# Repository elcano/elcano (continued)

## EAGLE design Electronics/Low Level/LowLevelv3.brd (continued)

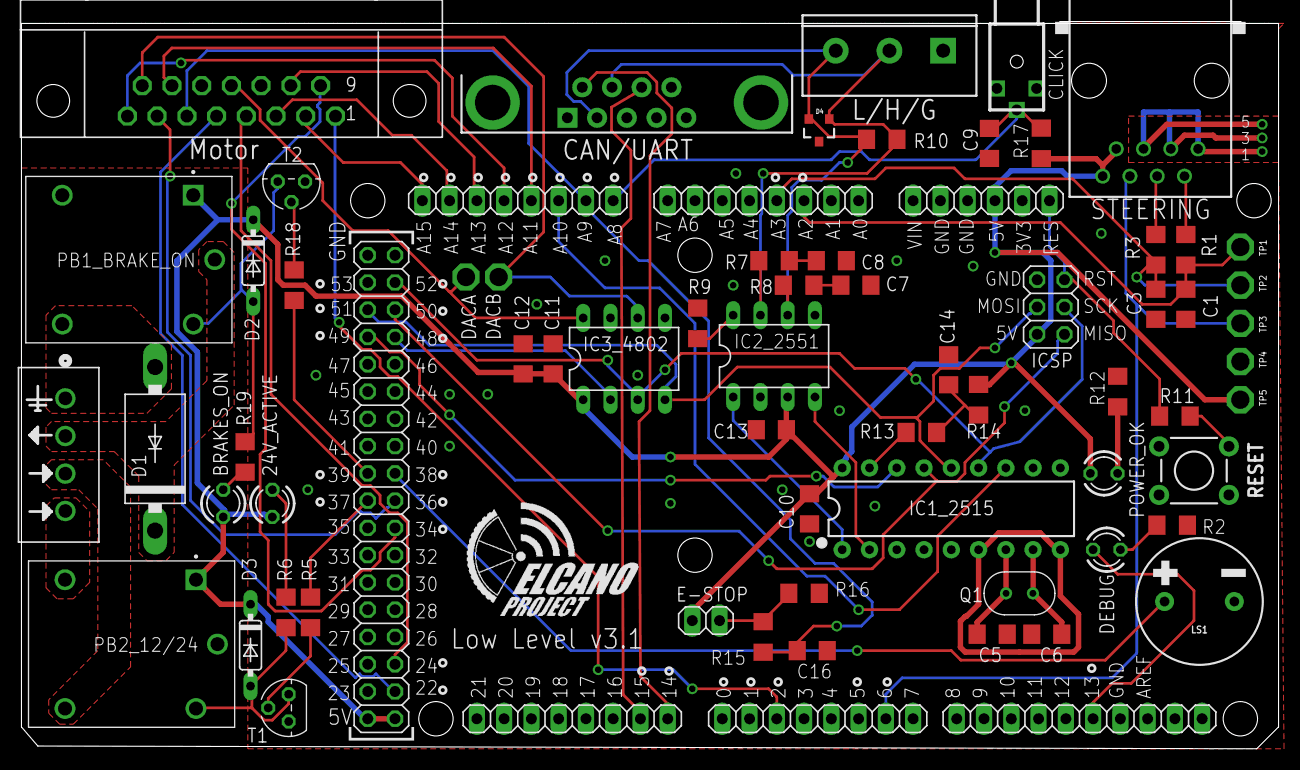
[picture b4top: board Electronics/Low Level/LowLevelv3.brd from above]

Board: 2 copper layers, 117.1 x 67.7 mm, 71 parts (0 on the bottom side), 60 nets.

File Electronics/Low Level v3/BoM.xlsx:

Qty | Device Name | Value | In BoM? | Digikey Part Number | Package | Part Label | Description | DESCRIPTION | DIGI-KEY_PART_NUMBER | DIGI-KEY_PURCHASE_URL | MANUFACTURER_PART_NUMBER | MF | MP | MPN | OC_FARNELL | OC_NEWARK | PACKAGE | PROD_ID | SF_SKU | SPICEPREFIX | VALUE | VENDOR
2 | 3mm green LED |  | yes | 732-5008-ND | LED3MM | 24V_ACTIVE, BRAKES_ON | LED
2 | C-USC1206 | 33pF | yes | 732-7873-1-ND | C1206 | C5, C6 | CAPACITOR, American symbol
2 | C-USC1206 | 560pF | yes | 311-4436-1-ND | C1206 | C7, C8 | CAPACITOR, American symbol
5 | C-USC1206 | 0.1uF | yes | 732-8086-1-ND | C1206 | C10, C11, C12, C13, C14 | CAPACITOR, American symbol
7 | C-USC1206 | 1uF | yes | 732-7685-1-ND | C1206 | C1, C2, C3, C4, C9, C15, C16 | CAPACITOR, American symbol
2 | R-US_R1206 | 100 | yes | 311-100FRCT-ND | R1206 | R7, R8 | RESISTOR, American symbol
6 | R-US_R1206 | 4.7K | yes | A106078CT-ND | R1206 | R1, R2, R3, R4, R9, R17 | RESISTOR, American symbol
4 | R-US_R1206 | 10k | yes | RMCF1206JT10K0CT-ND | R1206 | R11, R12, R15, R16 | RESISTOR, American symbol
1 | R-US_R1206 | 120 | yes | A129547CT-ND | R1206 | R10 | RESISTOR, American symbol
5 | R-US_R1206 | 1K | yes | RNCP1206FTD1K00CT-ND | R1206 | R5, R6, R13, R18, R19 | RESISTOR, American symbol
1 | R-US_R1206 | 20K | yes | RNCP1206FTD20K0CT-ND | R1206 | R14 | RESISTOR, American symbol
1 | 16MHz crystal | 16MHz | Yes | XC1759-ND | XTAL_ECS-160-20-46X | Q1 | QUARTZ CRYSTAL T/H | Crystal 16MHz ¬±30ppm _Tol_ ¬±50ppm _Stability_ 20pF FUND 50Ohm | XC1759-ND | https://www.digikey.com/product-detail/en/ecs-inc/ECS-160-20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 |  | ECS Inc. | ECS-160-20-46X |  |  |  | HC46/X ECS International |  |  | B
2 | 1N4148DO35-7 | 1N4148DO35-7 | yes | 1N4148FSCT-ND | DO35-7 | D2, D3 | DIODE
1 | 1N5400 | 1N5400 | yes | 1N5400-BDI-ND | DO201-15 | D1 | DIODE
1 | 284512-4 | 284512-4 | yes | A98398-ND | 284512-4 | X1 |  |  |  |  | 2845124 |  |  |  |  |  |  |  |  |  |  | TE Connectivity
2 | 2N3904 | 2N3904 | yes | 2N3904-APCT-ND | TO92 | T1, T2 | NPN TRANSISTOR
1 | BUZZER-PTH | BUZZER-PTH | Yes | 102-1153-ND | BUZZER-12MM | LS1 | Buzzer |  |  |  |  |  |  |  |  |  |  | COMP-08253 | COM-07950
2 | ORWH-SH-105D1F,000 | ORWH-SH-105D1F,000 | Yes | PB2032-ND | TE_ORWH-SH-105D1F,000 | PB1_BRAKE_ON, PB2_12/24 | General Purpose Relay, ORWH Series, Power, Non Latching, SPDT, 5 VDC, 10 A | General Purpose Relay, ORWH Series, Power, Non Latching, SPDT, 5 VDC, 10 A | PB2032-ND | https://www.digikey.com/product-detail/en/te-connectivity-po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 |  | TE | ORWH-SH-105D1F,000 |  |  |  | None
1 | ODO_JACK | CLICK |  |  | ODO_JACK | X4
1 | PESD1CAN | PESD1CAN | Yes | 1727-3817-1-ND | SPARKFUN-DISCRETESEMI_SOT23-3 | D4 | CAN bus ESD protection diode |  |  |  |  |  |  |  |  |  |  |  |  | J
1 | MCP2515(MCP2510)P | MCP2515 | yes | MCP2515-I/P-ND | DIP18 | IC1_2515 | CAN controller with SPI interface |  |  |  |  |  |  |  |  |  |  | NA-XXXXX |  | X | MCP2515
1 | MCP2551DIL08 | MCP2551DIL08 | Yes | MCP2551-E/P-ND‎ | IC-PACKAGE_DIL08 | IC2_2551 | CAN transceiver |  |  |  |  |  |  |  |  |  |  |  |  | X
1 | DIL8 | MCP4802 | Yes | MCP4802-E/P-ND | DIL08 | IC3_4802 | Dual In Line / Socket
1 | MOMENTARY-SWITCH-SPST-PTH-6.0MM | MOMENTARY-SWITCH-SPST-PTH-6.0MM | Yes | 450-1650-ND‎ | TACTILE_SWITCH_PTH_6.0MM | RESET | Momentary Switch (Pushbutton) - SPST |  |  |  |  |  |  |  |  |  |  | SWCH-08441 | COM-00097
1 | CONN_03-SCREW-5MM |  |  |  | SCREWTERMINAL-5MM-3 | CAN_HEADER | Multi connection point. Often used as Generic Header-pin footprint for 0.1 inch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 |  |  |  |  |  |  |  |  |  |  | CONN-10134 | PRT-08433
1 | 5-104069-4 | 5-104069-4 | yes | A107254-ND | CONN_5-104069-4_TYCO | STEERING_IO |  |  |  |  | 51040694 |  |  |  |  |  |  |  |  |  |  | TE Connectivity
1 | DB9FEMALE | DB9 Plug | Yes | 182-09ME-ND‎ | DB9 | CANBUS | DB9 Connector |  |  |  |  |  |  |  |  |  |  | CONN-08194 |  | X
1 | M15-182 | DB-15 | Yes | AE10976-ND | 182-015-MALE | X3 | SUB-D |  |  |  |  |  |  |  | unknown | unknown
1 | PINHD-1X2 |  |  |  | 1X02 | E-STOP | PIN HEADER
1 | PINHD-1X6 |  |  |  | 1X06 | POWER | PIN HEADER
1 | PINHD-2X3 | ICSP |  |  | 2X03 | ICSP | PIN HEADER
1 | PINHD-1X8 | Digital 0-7 |  |  | 1X08 | DIGITAL_0-7 | PIN HEADER
1 | PINHD-1X8 | Digital 14-21 |  |  | 1X08 | DIGITAL_14-21 | PIN HEADER
1 | PINHD-1X8 | Analog In 0-7 |  |  | 1X08 | ADCL | PIN HEADER
1 | PINHD-1X8 | Analog In 8-15 |  |  | 1X08 | ADCH | PIN HEADER
1 | PINHEAD_PINHD-2X18 | Digital 22-53 |  |  | PINHEAD_2X18 | MEGA_EXPANSION | PIN HEADER
1 | PINHD-1X10 | Digital 8-13 |  |  | 1X10 | DIGITAL_8-13 | PIN HEADER

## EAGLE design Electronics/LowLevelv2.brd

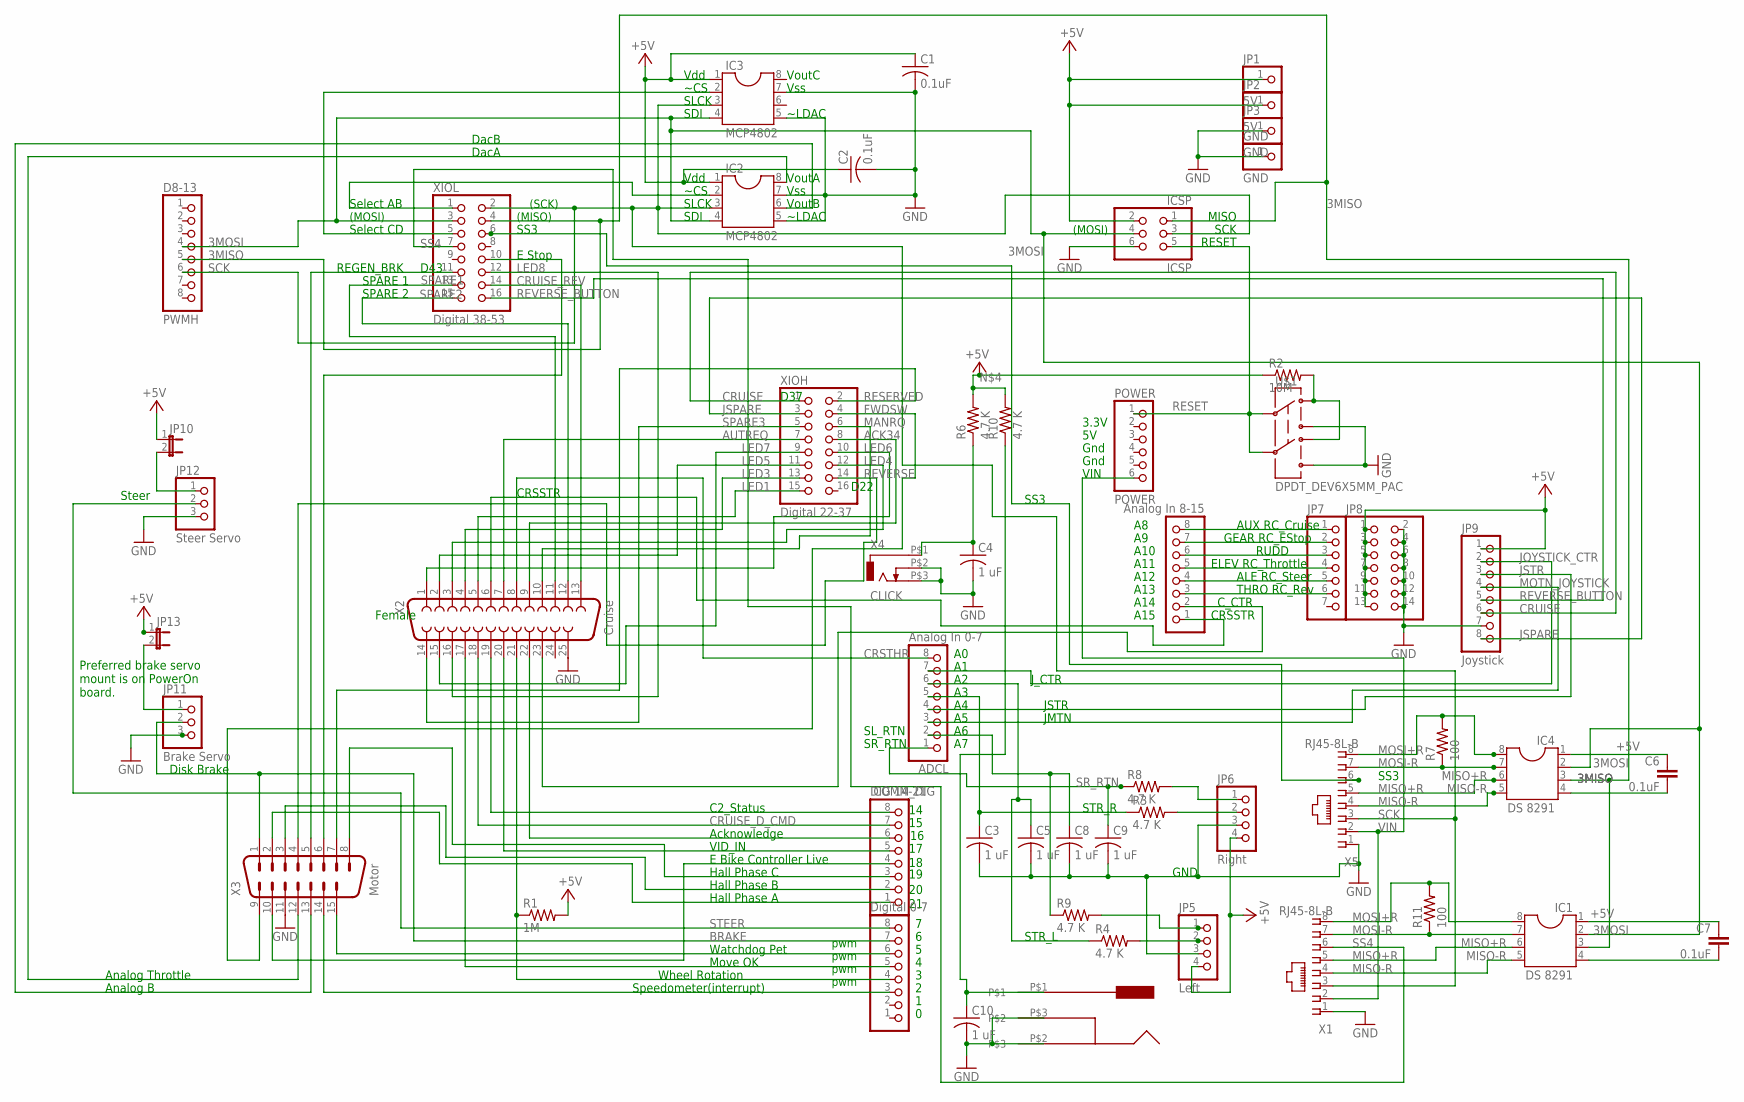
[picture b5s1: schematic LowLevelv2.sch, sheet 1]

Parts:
ADCH: Analog In 8-15; 1X08
ADCL: Analog In 0-7; 1X08
C1, C2: 0.1uF; C025-025X050
C3, C4, C5, C8, C9, C10: 1 uF; C025-030X050
C6, C7: 0.1uF; C2.5-2
COMM_DIG: DIG 14-21; 1X08
D8-13: PWMH; 1X08
GND: GND; 1X01
IC1, IC4: DS 8291; DIL08
IC2, IC3: MCP4802; DIL08
ICSP: ICSP; 2X03
JP1, JP2: 5V; 1X01
JP3: GND; 1X01
JP5: Left; 1X04/90
JP6: Right; 1X04/90
JP7: PINHD-1X7; 1X07
JP8: PINHD-2X7; 2X07
JP9: Joystick; 1X08/90
JP10, JP13: JP1E; JP1
JP11: Brake Servo; 1X03/90
JP12: Steer Servo; 1X03/90
POWER: POWER; 1X06
PWML: Digital 0-7; 1X08
R1: 1M; 0207/10
R2: 10M; 0207/10
R3, R4, R6, R8, R9, R10: 4.7 K; 0207/10
R7, R11: 100; 0207/10
U$1: DPDT_DEV6X5MM_PAC; NEWSWITCH2_PAC
U$2: CUI_JACKTHROUGH_HOLE; CUIJACK
X1, X5: RJ45-8L-B; RJ45-NO-SHIELD
X2: Cruise; F25H
X3: Motor; 182-015-MALE
X4: CLICK; ODO_JACK
XIOH: Digital 22-37; 2X08
XIOL: Digital 38-53; 2X08

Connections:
1C: ADCH.6, JP7.3
3A: ADCH.3, JP7.6
3MISO: D8-13.5, IC1.3, IC4.3, ICSP.1, XIOL.4
3MOSI: D8-13.4, IC1.2, IC2.4, IC3.4, IC4.2, ICSP.4, XIOL.3
5V: JP10.2, JP12.1
5VOLT: JP11.1, JP13.2
+5V: C1.1, C2.1, C6.1, IC2.1, IC3.1, IC4.1, ICSP.2, JP1.1, JP2.1, JP5.4, JP6.4, JP8.1, JP8.3, JP8.5, JP8.7, JP8.9, JP8.11, JP8.13, JP9.1, JP10.1, JP13.1, R1.2, R2.1, R6.2, R10.2
A14: ADCH.7, JP7.2
A15: ADCH.8, JP7.1
ACK34: X2.9, XIOH.8
ACKNOWLEDGE: COMM_DIG.6, X2.22
AUTREQ: X2.7, XIOH.7
BRAKE: JP11.2, PWML.7, X3.1
C2STATUS: COMM_DIG.8, X2.19
CRSSTR: ADCH.1, X2.6
CRSTHR: ADCL.8, X2.8
CRUISE: JP9.6, XIOH.1
CRUISE_D_CMD: COMM_DIG.7, X2.18
CRUISE_REV: X2.13, XIOL.14
C_CTR: ADCH.2, X2.23
DACA: IC2.8, X3.12
DACB: IC2.6, X3.13
EBIKECONTRL: COMM_DIG.4, X3.10
ESTOP: X3.6, XIOL.10
FWDSW: X3.9, XIOH.4
GND: C1.2, C2.2, C3.2, C4.2, C5.2, C8.2, C9.2, C10.2, GND.1, IC2.5, IC2.7, IC3.5, IC3.7, ICSP.6, JP3.1, JP5.3, JP6.3, JP8.2, JP8.4, JP8.6, JP8.8, JP8.10, JP8.12, JP8.14, JP9.7, JP11.3, JP12.3, U$1.PIN3 (3), U$1.PIN6 (6), U$2.P$2, U$2.P$3, X1.1, X2.25, X3.11, X4.P$2 (2), X4.P$3 (3), X5.1
HALLPHASEA: COMM_DIG.1, X3.2
HALLPHASEB: COMM_DIG.2, X3.3
HALLPHASEC: COMM_DIG.3, X3.8
JOYSTICK_CTR: ADCL.7, JP9.2
JSPARE: JP9.8, XIOH.3
JSTR: ADCL.4, JP9.3
LED1: X2.5, XIOH.15
LED3: X2.4, XIOH.13
LED4: X2.3, XIOH.12
LED5: X2.2, XIOH.11
LED6: X2.1, XIOH.10
LED7: X2.15, XIOH.9
LED8: X2.16, XIOL.12
L_STR: JP5.2, R4.2
MANRQ: X2.10, XIOH.6
MISO+R: IC1.6, IC4.6, X1.5, X5.5
MISO-R: IC1.5, IC4.5, X1.4, X5.4
MOSI+R: IC1.8, IC4.8, R7.2, R11.2, X1.8, X5.8
MOSI-R: IC1.7, IC4.7, R7.1, R11.1, X1.7, X5.7
MOTN_JOYSTICK: ADCL.3, JP9.4
MOVEOK: PWML.5, X2.17
unnamed: C10.1, R10.1, U$2.P$1
unnamed: C6.2, IC4.4
unnamed: C7.2, IC1.4
unnamed: C4.1, R6.1, X4.P$1 (1)
unnamed: C7.1, IC1.1
unnamed: R2.2, U$1.PIN1 (1), U$1.PIN4 (4)
unnamed: ADCH.4, JP7.5
unnamed: ADCH.5, JP7.4
REGENBAKE: X3.5, XIOL.11
RESERVED: X3.7, XIOH.2
RESET: ICSP.5, POWER.1, U$1.PIN2 (2), U$1.PIN5 (5)
REVERSE: X3.4, XIOH.14
REVERSE_BUTTON: JP9.5, XIOL.16
R_STR: JP6.2, R3.2
SCK: D8-13.6, IC2.3, IC3.3, ICSP.3, X1.3, X5.3, XIOL.2
SELECTAB: IC2.2, XIOL.1
SELECTCD: IC3.2, XIOL.5
SL_RET: JP5.1, R9.2
SL_RTN: ADCL.2, C8.1, R9.1
SPARE1: X2.11, XIOL.13
SPARE2: X2.12, XIOL.15
SPARE3: X2.14, XIOH.5
SPEEDOMETER: PWML.3, X3.14
SR_RET: JP6.1, R8.2
SR_RTN: ADCL.1, C9.1, R8.1
SS3: X5.6, XIOL.6
SS4: X1.6, XIOL.7
STEER: JP12.2, PWML.8
STR_L: ADCL.6, C5.1, R4.1
STR_R: ADCL.5, C3.1, R3.1
VIDIN: COMM_DIG.5, X2.20
VIN: POWER.6, X1.2, X5.2
WATCHDOG: PWML.6, X3.15
WHEELROTATION: PWML.4, R1.1, X2.21

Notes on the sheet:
(MOSI)
pwm
(SCK)
(MISO)
Move OK
Disk Brake
Gnd
Steer
Acknowledge
VID_IN
C2_Status
REGEN_BRK
Female
Vdd
~CS
SLCK
VoutA
Vss
VoutB
~LDAC
VoutC
Select AB
Select CD
Watchdog Pet
Analog B
Analog Throttle
SDI
DacA
DacB
D43
3.3V
MISO
SCK
RESET
VIN
Wheel Rotation
Speedometer(interrupt)
AUX RC_Cruise
RUDD
ELEV RC_Throttle

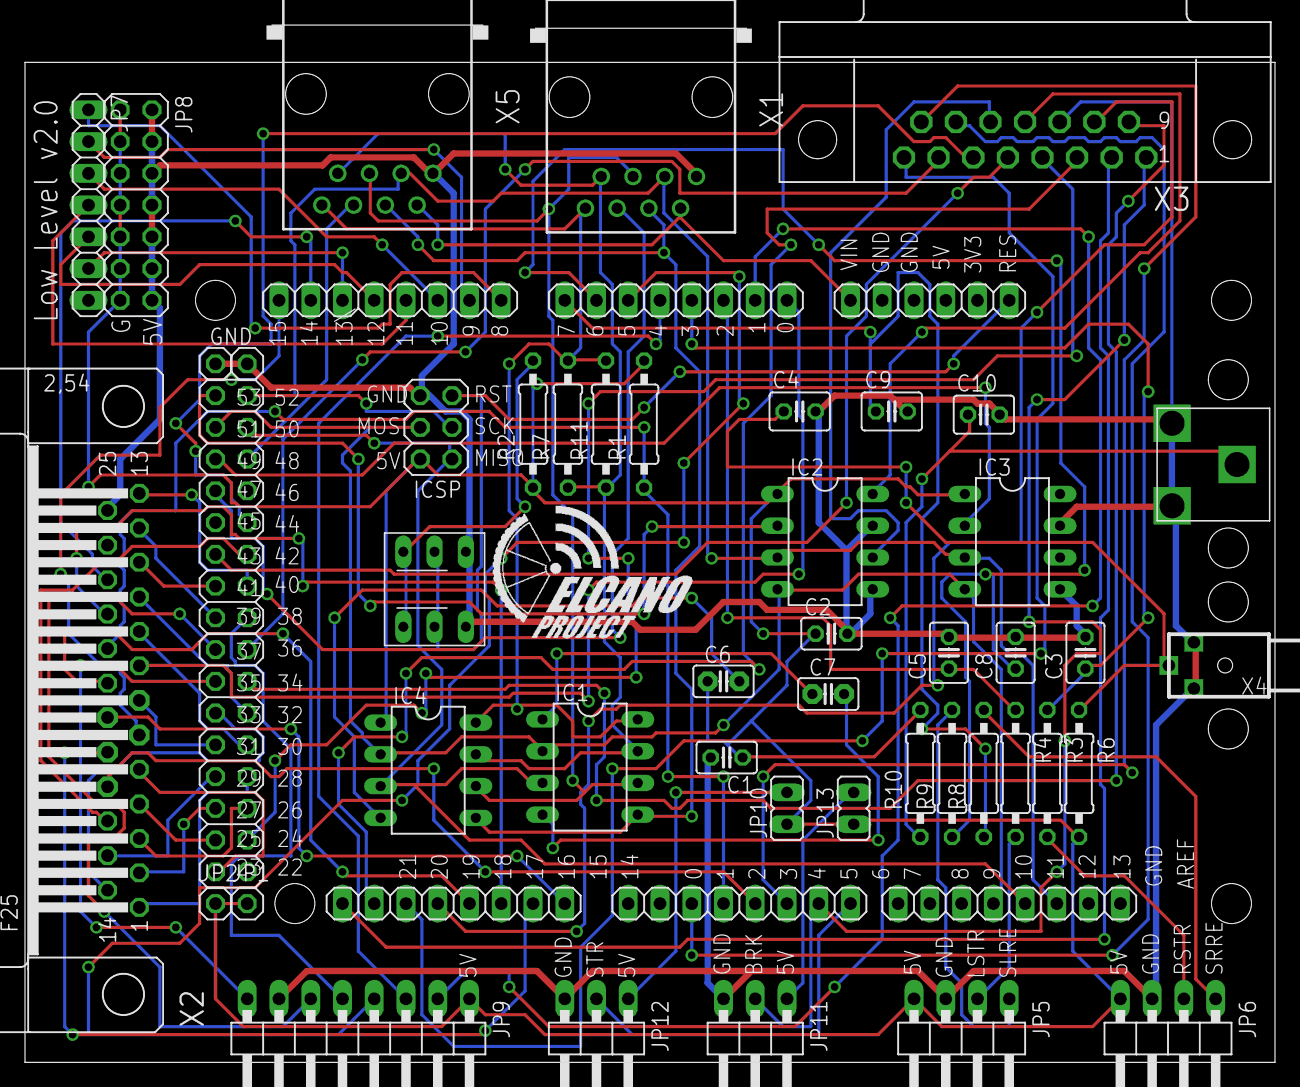
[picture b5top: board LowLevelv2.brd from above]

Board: 2 copper layers, 100.0 x 83.0 mm, 53 parts (0 on the bottom side), 81 nets.

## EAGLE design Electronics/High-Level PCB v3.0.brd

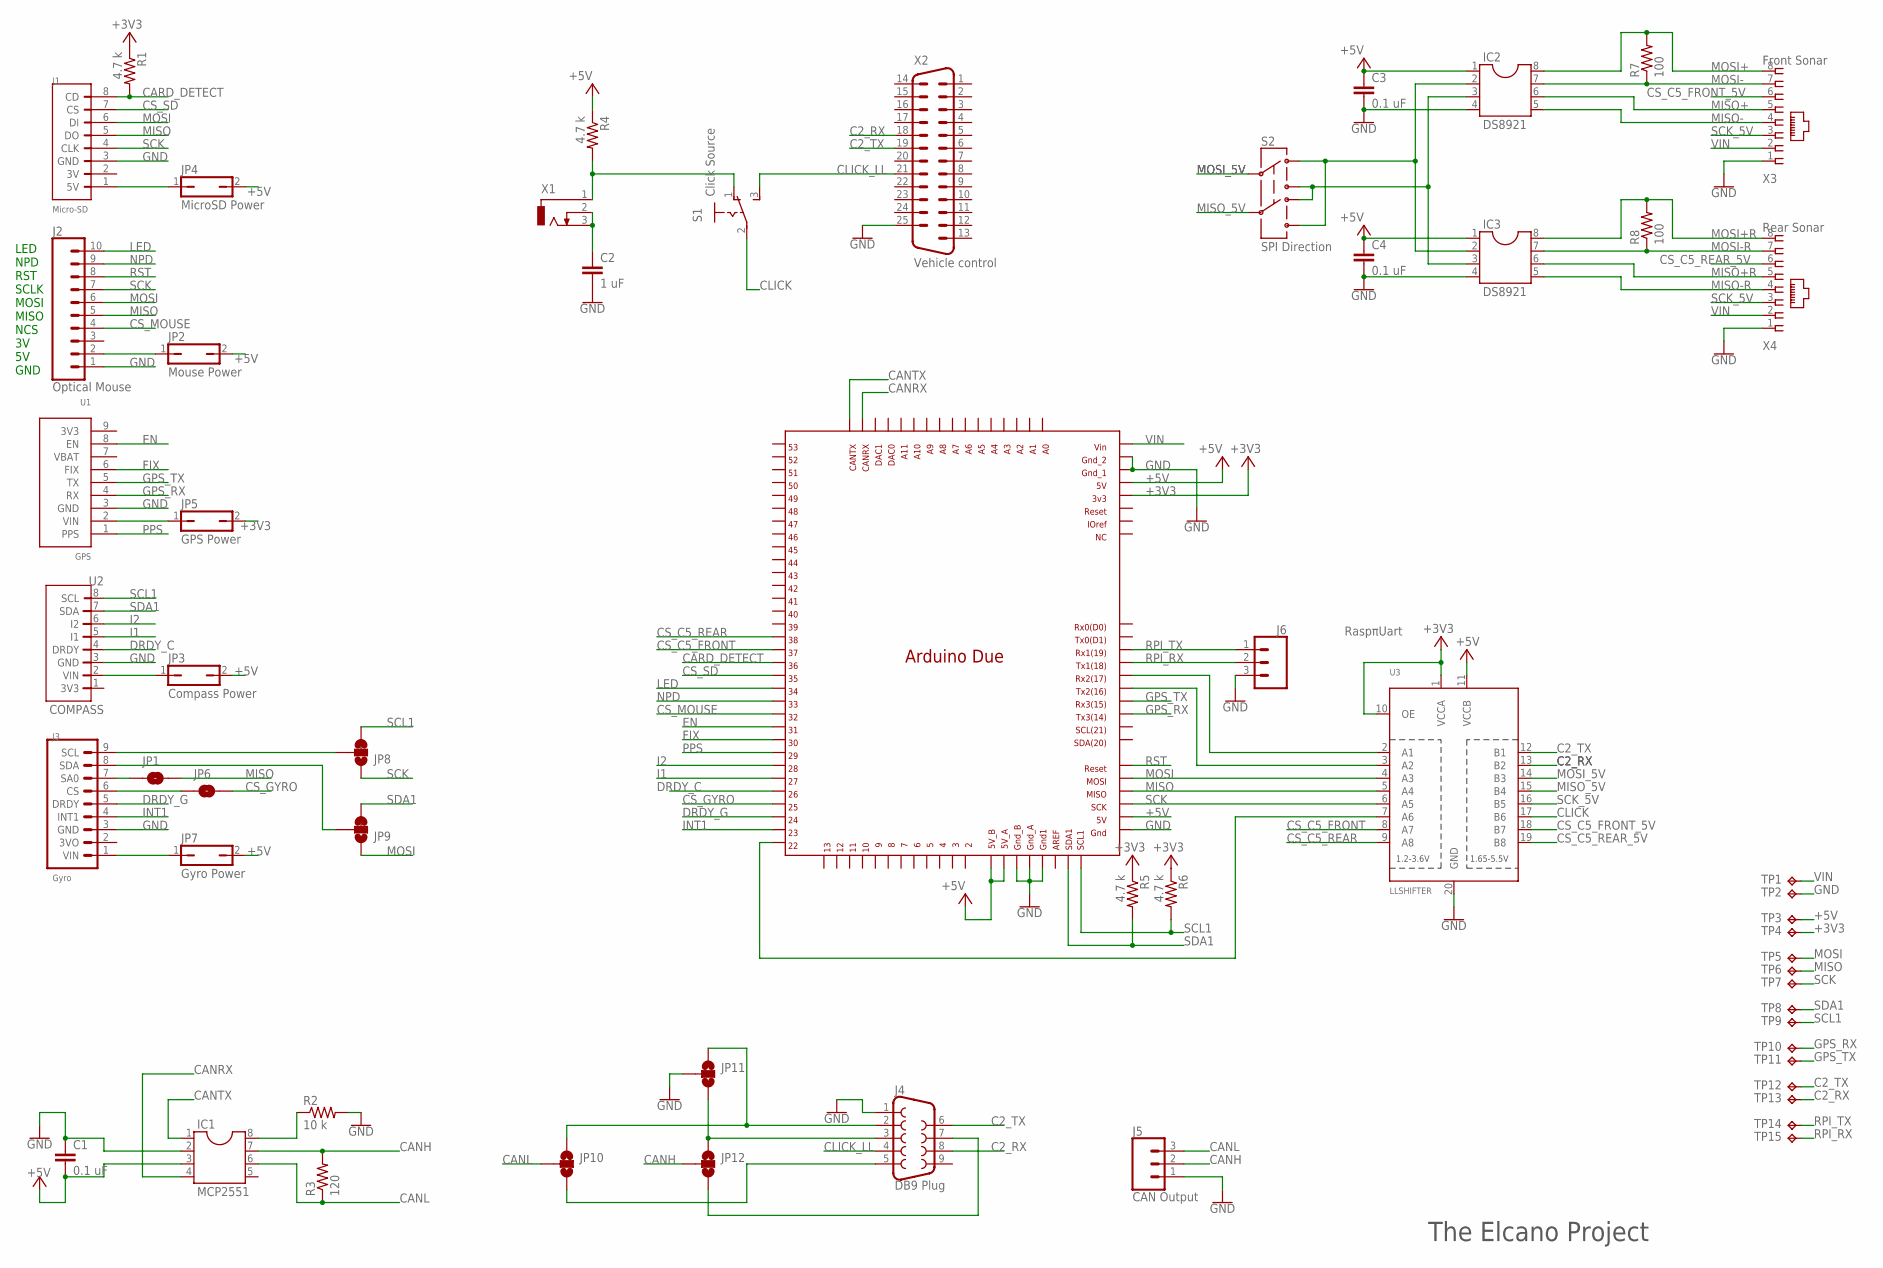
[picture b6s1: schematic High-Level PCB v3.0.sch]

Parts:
C1, C3, C4: 0.1 uF; C2.5-5
C2: 1 uF; C2.5-5
IC1: MCP2551; DIL08
IC2, IC3: DS8921; DIL08
J1: Micro-SD; ELSDCARD
J2: Optical Mouse; 1X10
J3: Gyro; ELGYRO
J4: DB9 Plug; DB9_MALE
J5: CAN Output; SCREWTERMINAL-5MM-3
J6: RaspπUart; 1X03
JP1, JP6: JUMPER-SMT_2_NO_SILK; SMT-JUMPER_2_NO_SILK
JP2: Mouse Power; JP1
JP3: Compass Power; JP1
JP4: MicroSD Power; JP1
JP5: GPS Power; JP1
JP7: Gyro Power; JP1
JP8, JP9: JUMPER-SMT_3_1-NC_TRACE_SILK; SMT-JUMPER_3_1-NC_TRACE_SILK
JP10, JP11, JP12: JUMPER-SMT_3_NO_SILK; SMT-JUMPER_3_NO_SILK
MCU1: DUE(NORMAL)
R1, R4, R5, R6: 4.7 k; 0204/7
R2: 10 k; 0204/7
R3: 120; 0204/7
R7, R8: 100; 0204/7
S1: Click Source; SP_ELSWITCH
S2: SPI Direction; DPDT
TP1, TP2, TP3, TP4, TP5, TP6, TP7, TP8, TP9, TP10, TP11, TP12, TP13, TP14, TP15: TPPAD1-17; P1-17
U1: GPS; ELGPS
U2: COMPASS; ELCOMPASS
U3: LLSHIFTER; ELSHIFTER
X1: 2.5MMJACK
X2: Vehicle control; M25H
X3: Front Sonar; RJ45-NO-SHIELD
X4: Rear Sonar; RJ45-NO-SHIELD

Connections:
+3V3: JP5.2, MCU1.3V3, R1.1, R5.1, R6.1, TP4.TP, U3.1 (VCCA), U3.10 (OE)
+5V: C1.2, C3.1, C4.1, IC1.3, IC2.1, IC3.1, JP2.2, JP3.2, JP4.2, JP7.2, MCU1.5V, MCU1.5V_A, MCU1.5V_B, MCU1.GND_ICSP, R4.1, TP3.TP, U3.11 (VCCB)
C2_RX: J4.8, TP13.TP, U3.13 (B2), X2.18
C2_TX: J4.6, TP12.TP, U3.12 (B1), X2.19
CANH: IC1.7, J5.2, JP12.2, R3.2
CANL: IC1.6, J5.3, JP10.2, R3.1
CANRX: IC1.4, MCU1.CANRX
CANTX: IC1.1, MCU1.CANTX
CARD_DETECT: J1.8 (CD), MCU1.36, R1.2
CLICK: S1.2, U3.17 (B6)
CLICK_LL: J4.4, S1.3 (S), X2.21
CS_C5_FRONT: MCU1.37, U3.8 (A7)
CS_C5_FRONT_5V: U3.18 (B7), X3.6
CS_C5_REAR: MCU1.38, U3.9 (A8)
CS_C5_REAR_5V: U3.19 (B8), X4.6
CS_GYRO: JP6.2, MCU1.25
CS_MOUSE: J2.4, MCU1.32
CS_SD: J1.7 (CS), MCU1.35
DRDY_C: MCU1.26, U2.4 (DRDY)
DRDY_G: J3.5 (DRDY), MCU1.24
EN: MCU1.31, U1.8 (EN)
FIX: MCU1.30, U1.6 (FIX)
GND: C1.1, C2.2, C3.2, C4.2, IC1.2, IC2.4, IC3.4, J1.3 (GND), J2.1, J3.3 (GND), J4.1, J5.1, J6.3, JP11.2, MCU1.5V_ICSP, MCU1.GND1, MCU1.GND_1, MCU1.GND_2, MCU1.GND_A, MCU1.GND_B, R2.2, TP2.TP, U1.3 (GND), U2.3 (GND), U3.20 (GND), X2.25, X3.1, X4.1
GPS_RX: MCU1.TX3, TP10.TP, U1.4 (RX)
GPS_TX: MCU1.RX3, TP11.TP, U1.5 (TX)
I1: MCU1.27, U2.5 (I1)
I2: MCU1.28, U2.6 (I2)
INT1: J3.4 (INT1), MCU1.23
LED: J2.10, MCU1.34
MISO: J1.5 (DO), J2.5, JP1.2, MCU1.MISO_ICSP, TP6.TP, U3.5 (A4)
MISO+: IC2.6, X3.5
MISO+R: IC3.6, X4.5
MISO-: IC2.5, X3.4
MISO-R: IC3.5, X4.4
MISO_5V: S2.5, U3.15 (B4)
MOSI: J1.6 (DI), J2.6, JP9.1, MCU1.MOSI_ICSP, TP5.TP, U3.4 (A3)
MOSI+: IC2.8, R7.2, X3.8
MOSI+R: IC3.8, R8.2, X4.8
MOSI-: IC2.7, R7.1, X3.7
MOSI-R: IC3.7, R8.1, X4.7
MOSI_5V: S2.2, U3.14 (B3)
unnamed: C2.1, X1.2, X1.3
unnamed: IC2.2, IC3.2, S2.1, S2.6
unnamed: IC2.3, IC3.3, S2.3, S2.4
unnamed: MCU1.TX2, U3.3 (A2)
unnamed: MCU1.RX2, U3.2 (A1)
unnamed: R4.2, S1.1 (O), X1.1
unnamed: JP3.1, U2.2 (VIN)
unnamed: J3.1 (VIN), JP7.1
unnamed: J1.1 (5V), JP4.1
unnamed: J4.3, JP11.3, JP12.1
unnamed: MCU1.22, U3.7 (A6)
unnamed: J2.2, JP2.1
unnamed: JP5.1, U1.2 (VIN)
unnamed: J4.5, JP10.3
unnamed: J4.7, JP12.3
unnamed: IC1.8, R2.1
unnamed: J4.2, JP10.1, JP11.1
unnamed: J3.6 (CS), JP6.1
unnamed: J3.7 (SA0), JP1.1
unnamed: J3.8 (SDA), JP9.2
unnamed: J3.9 (SCL), JP8.2
NPD: J2.9, MCU1.33
PPS: MCU1.29, U1.1 (PPS)
RPI_RX: J6.2 (1), MCU1.TX1, TP15.TP
RPI_TX: J6.1 (2), MCU1.RX1, TP14.TP
RST: J2.8, MCU1.RESET_ICSP
SCK: J1.4 (CLK), J2.7, JP8.1, MCU1.SCK_ICSP, TP7.TP, U3.6 (A5)
SCK_5V: U3.16 (B5), X3.3, X4.3
SCL1: JP8.3, MCU1.SCL1, R6.2, TP9.TP, U2.8 (SCL)
SDA1: JP9.3, MCU1.SDA1, R5.2, TP8.TP, U2.7 (SDA)
VIN: MCU1.VIN, TP1.TP, X3.2, X4.2

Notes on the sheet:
LED NPD RST SCLK MOSI MISO NCS 3V 5V GND
The Elcano Project

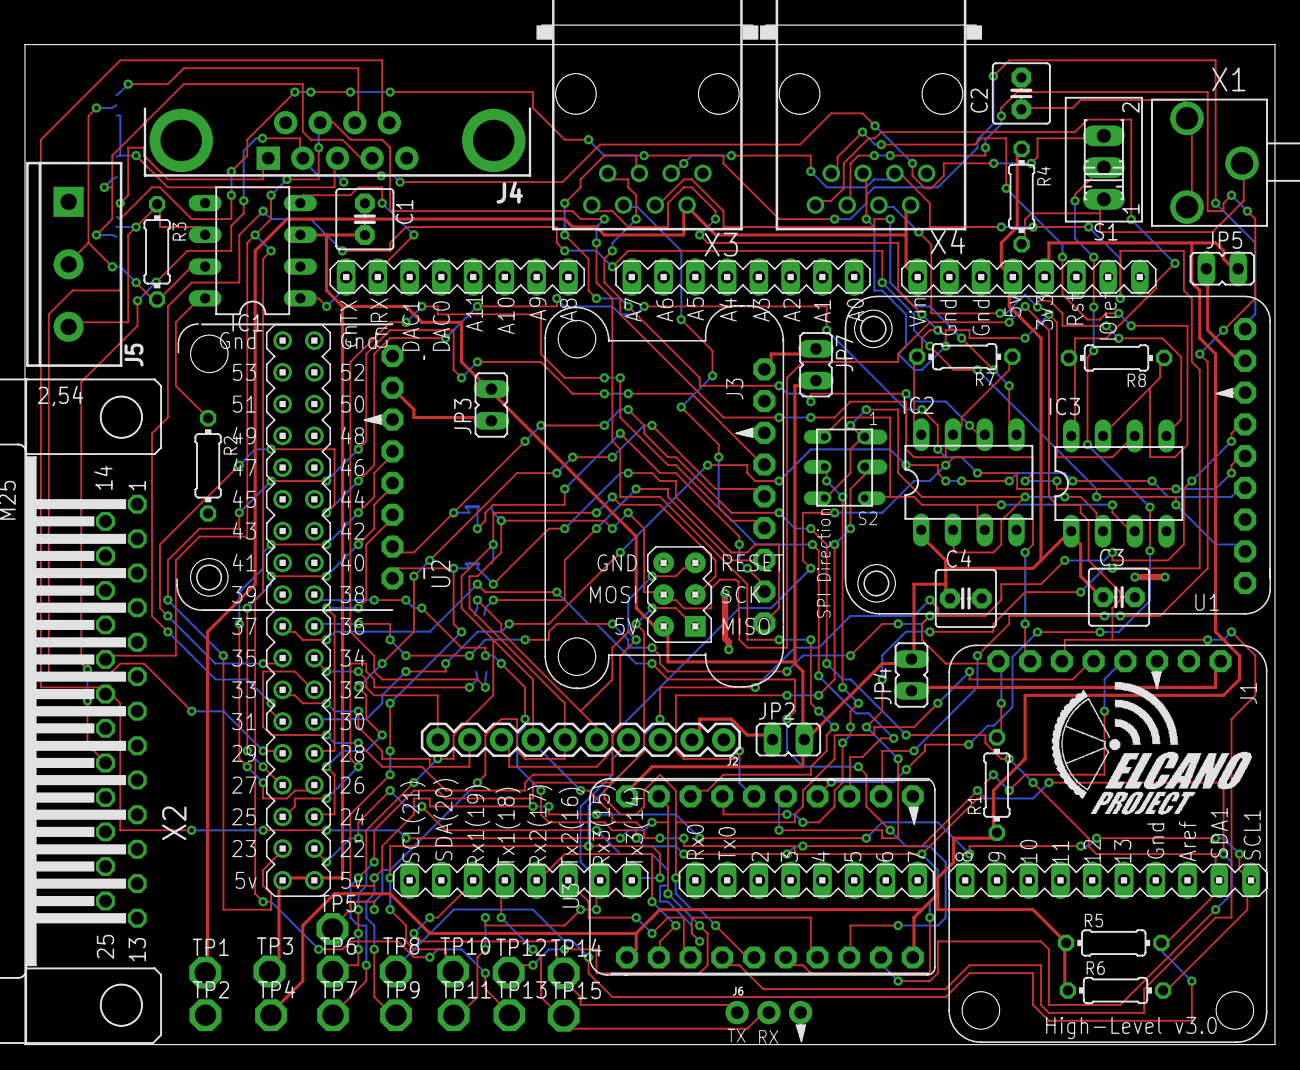
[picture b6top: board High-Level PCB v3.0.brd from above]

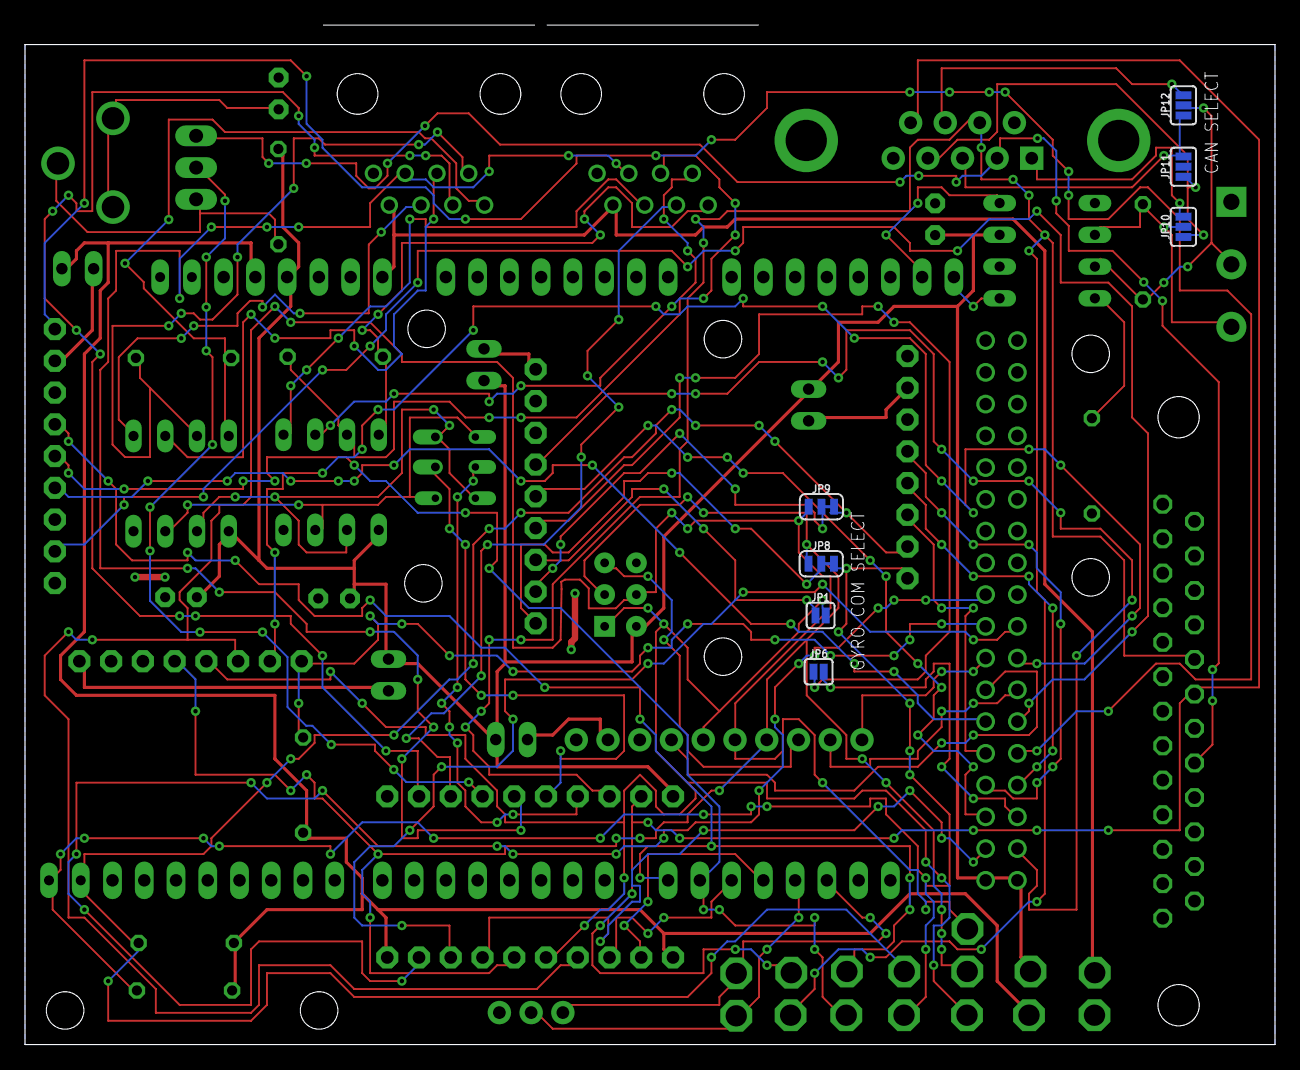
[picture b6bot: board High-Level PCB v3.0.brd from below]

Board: 2 copper layers, 100.0 x 81.6 mm, 58 parts (7 on the bottom side), 72 nets.

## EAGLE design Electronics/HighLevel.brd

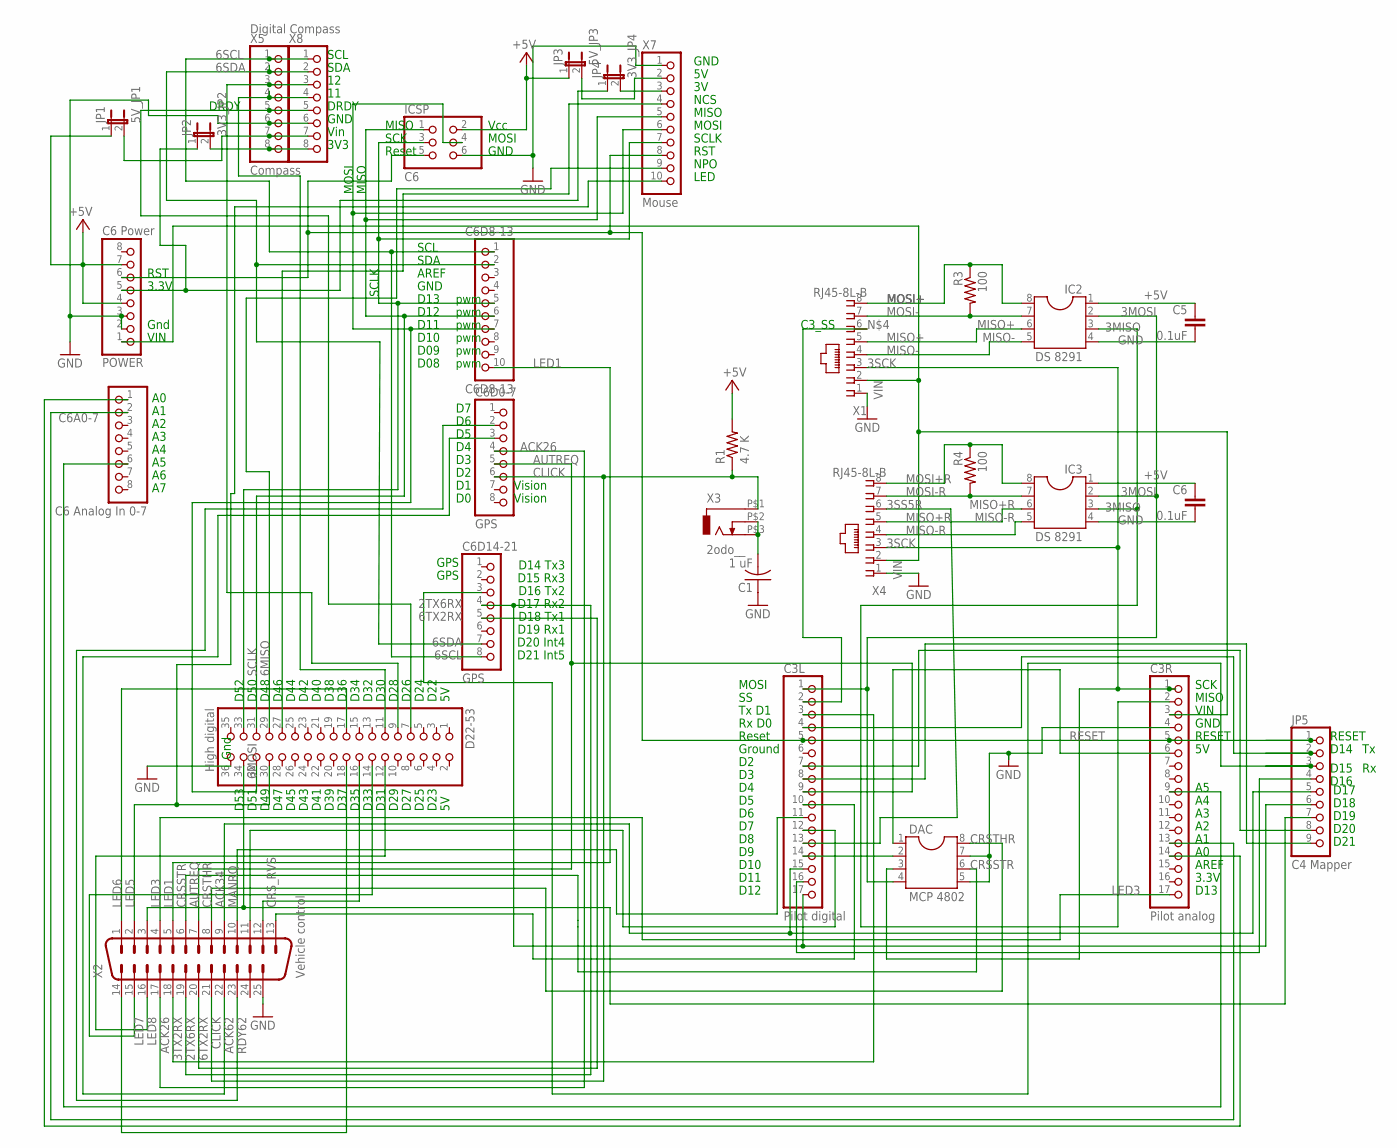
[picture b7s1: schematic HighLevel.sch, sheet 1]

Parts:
C1: 1 uF; C025-030X050
C3L: Pilot digital; 1X17
C3R: Pilot analog; 1X17
C5, C6: 0.1uF; C2.5-2
C6A0-7: C6 Analog In 0-7; 1X08
C6D0-7, C6D14-21: GPS; 1X08
C6D8-13: C6D8-13; 1X10
D22-53: High digital; 2X18
DAC: MCP 4802; DIL08
IC2, IC3: DS 8291; DIL08
ICSP: C6; 2X03
JP1: 5V_JP1; JP1
JP2: 3V3_JP2; JP1
JP3: 5V_JP3; JP1
JP4: 3V3_JP4; JP1
JP5: C4 Mapper; 1X09
POWER: C6 Power; 1X08
R1: 4.7 K; 0207/10
R3, R4: 100; 0204/5
X1, X4: RJ45-8L-B; RJ45-NO-SHIELD
X2: Vehicle control; M25H
X3: 2odo__; ODO_JACK
X5: Compass; 1X08
X7: Mouse; 1X10
X8: Digital Compass; 1X08

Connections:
2TX6RX: C3L.17, C6D14-21.4, JP5.6, X2.19
3MISO: C3R.2, IC2.3, IC3.3
3MOSI: C3L.1, DAC.4, IC2.2, IC3.2
3SCK: C3R.1, DAC.3, X1.3, X4.3
3SCL: C3L.8, JP5.9
3SDA: C3L.7, JP5.8
3SS5R: C3L.13, X4.6
3SS_DAC: C3L.14, DAC.2
3TX2RX: C3L.3, X2.18
3V3: JP2.1, JP4.1, POWER.5
3VLSM: JP2.2, X5.8, X8.8
5VLSM: JP1.2, X5.7, X8.7
5V_C3: C3R.6, DAC.1
6MISO: C6D8-13.6, D22-53.31, ICSP.1, X7.5
6MOSI: C6D8-13.7, D22-53.32, ICSP.4, X7.6
6SCL: C6D8-13.1, C6D14-21.8, X5.1, X8.1
6SDA: C6D8-13.2, C6D14-21.7, X5.2, X8.2
6TX2RX: C6D14-21.5, X2.20
+5V: C5.1, C6.1, IC2.1, IC3.1, ICSP.2, JP1.1, JP3.1, POWER.4, POWER.7, R1.2
A0: C3R.14, C6A0-7.1
A1: C3R.13, C6A0-7.2
A5: C3R.9, C6A0-7.6
ACK26: C6D0-7.4, X2.17
ACK34: C3L.15, JP5.5, X2.9
ACK43: C3L.16, JP5.4
ACK62: C6D0-7.3, X2.22
AUTREQ: C3L.9, C6D0-7.5, X2.7
CLICK: C6D0-7.6, R1.1, X2.21, X3.P$1 (1)
CRSSTR: DAC.6, X2.6
CRSTHR: DAC.8, X2.8
CRS_RVS: C3L.10, X2.13
D09: D22-53.18, X2.14
DRDY: D22-53.7, X5.5, X8.5
GND: C1.1, C3R.4, C5.2, C6.2, D22-53.36, DAC.5, DAC.7, IC2.4, IC3.4, ICSP.6, POWER.2, POWER.3, X1.1, X2.25, X4.1, X5.6, X7.1, X8.6
I1LSM: D22-53.11, X5.4, X8.4
I2LSM: D22-53.9, X5.3, X8.3
LED1: C6D8-13.10, X2.5
LED3: C3R.17, X2.4
LED4: D22-53.34, JP5.7, X2.3
LED5: D22-53.30, X2.2, X7.10
LED6: D22-53.17, X2.1
LED7: D22-53.14, X2.15
LED8: D22-53.12, X2.16
M3V: JP4.2, X7.3
M5V: JP3.2, X7.2
MANRQ: C3L.11, X2.10
MISO+: IC2.6, X1.5
MISO+R: IC3.6, X4.5
MISO-: IC2.5, X1.4
MISO-R: IC3.5, X4.4
MOSI+: IC2.8, R3.1, X1.8
MOSI+R: IC3.8, R4.1, X4.8
MOSI-: IC2.7, R3.2, X1.7
MOSI-R: IC3.7, R4.2, X4.7
unnamed: C3L.2, X1.6
unnamed: C1.2, X3.P$2 (2), X3.P$3 (3)
NAV_FIX: C6D14-21.3, JP5.3
NCS: D22-53.27, X7.4
NPO: D22-53.29, X7.9
PATH: C3L.4, JP5.2
RDY26: D22-53.16, X2.12
RDY32: C3L.12, X2.11
RDY62: C6D0-7.2, X2.23
RESET: C3L.5, C3R.5, ICSP.5, JP5.1, POWER.6, X7.8
SCLK: C6D8-13.5, D22-53.33, ICSP.3, X7.7
VIN: C3R.3, POWER.1, X1.2, X4.2

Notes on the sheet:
pwm
Gnd
D10
D11
D12
D13
D09
D08
VIN
Rx D0
Tx D1
Reset
Ground
D14 Tx3
D15 Rx3
D16 Tx2
D17 Rx2
D18 Tx1
D19 Rx1
D20 Int4
D21 Int5
MISO
MOSI
SCLK
SCK
Vcc
GND
D52
D22
RST
C3_SS
3.3V
AREF
DRDY
GPS
Vision
D27
D29
D31
D25

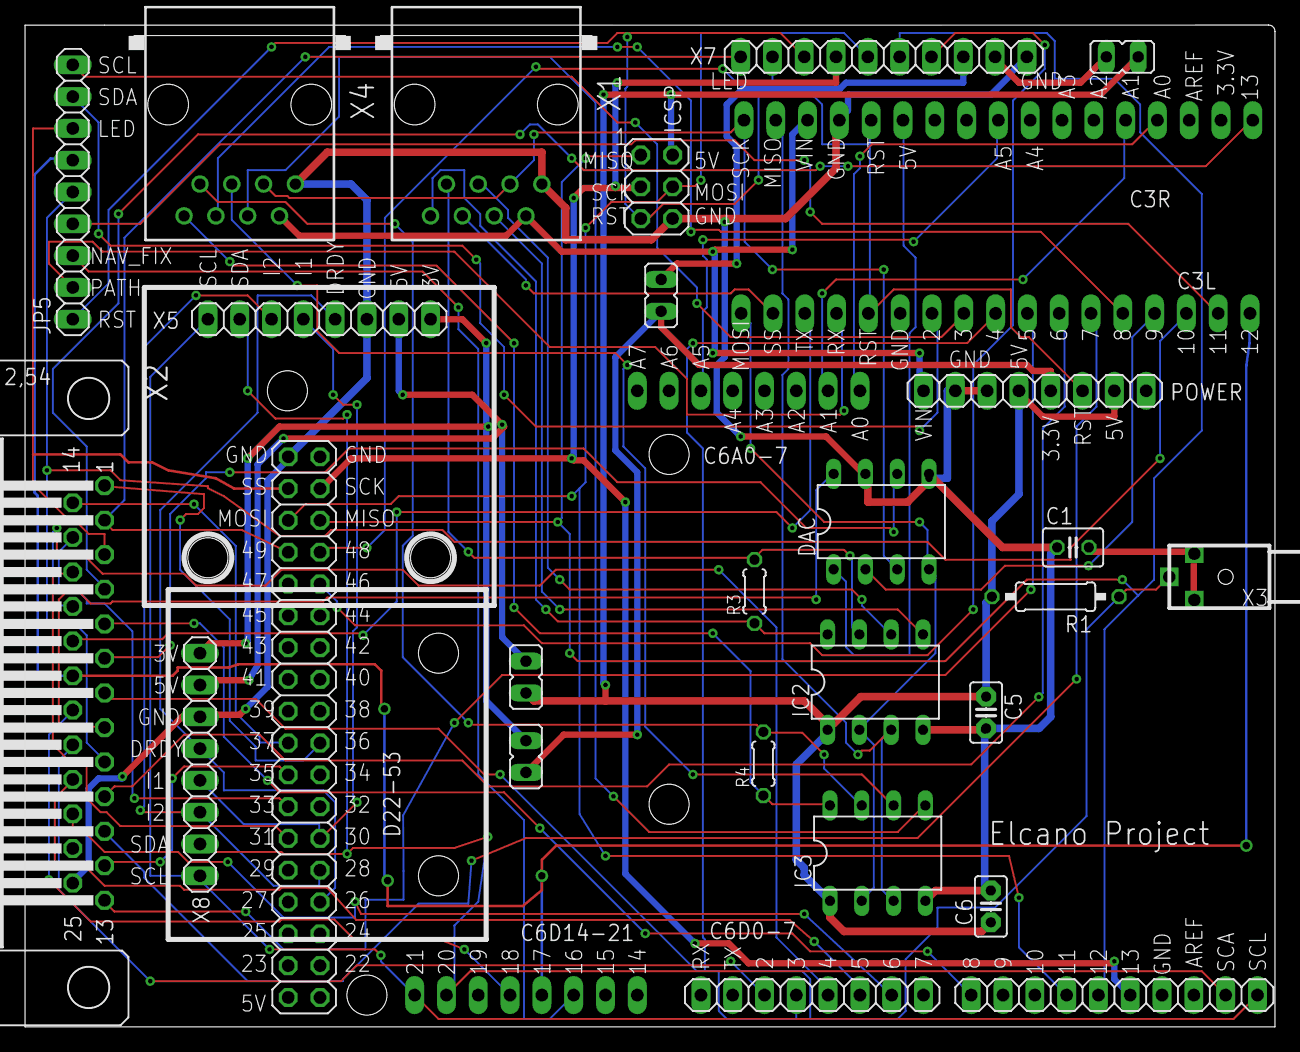
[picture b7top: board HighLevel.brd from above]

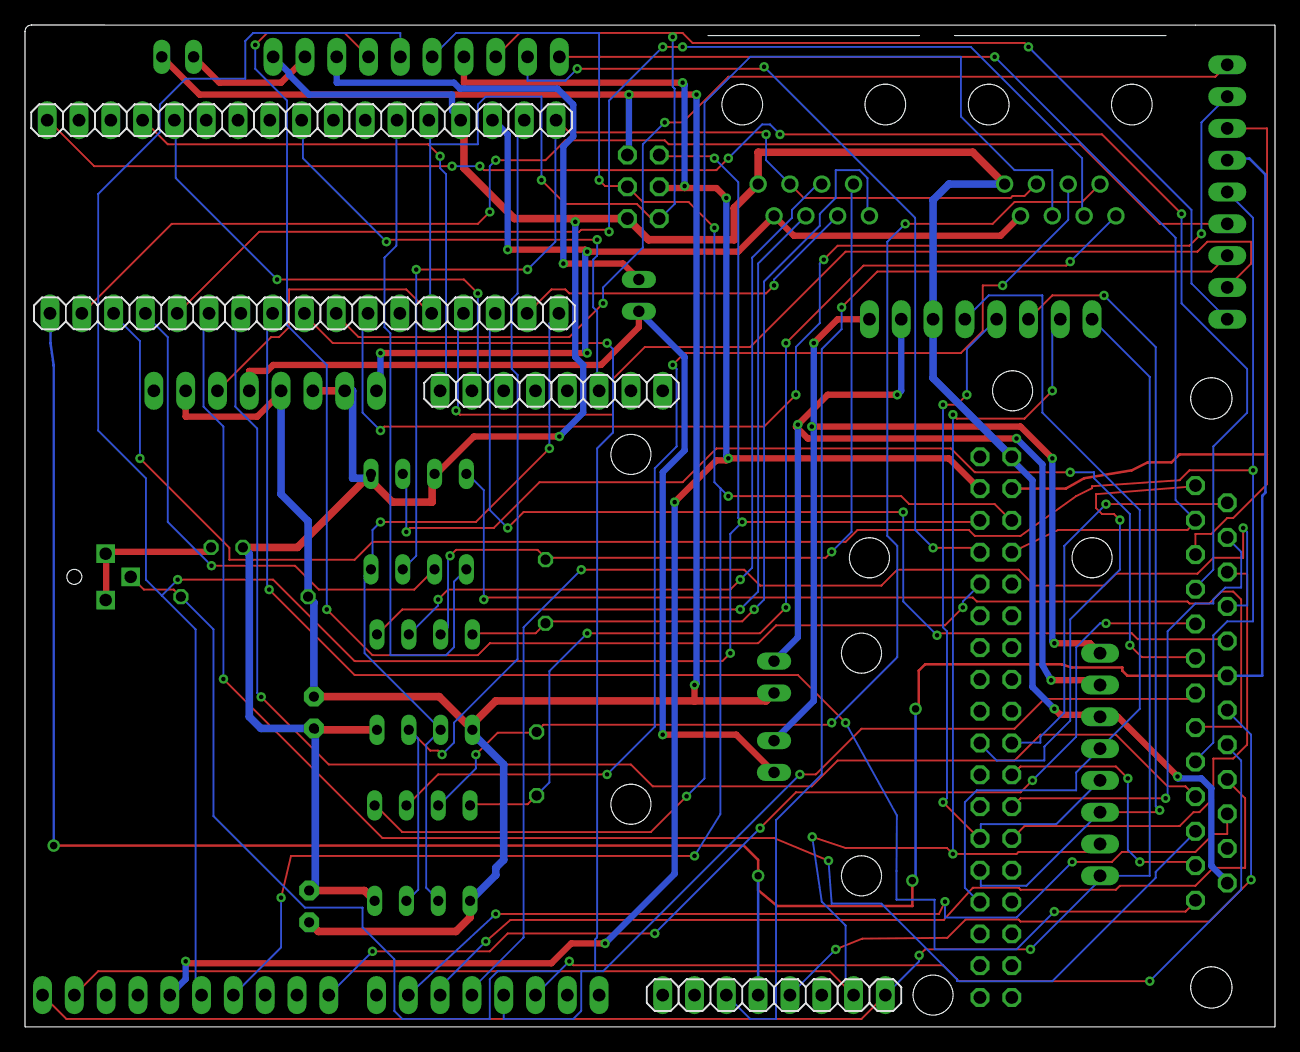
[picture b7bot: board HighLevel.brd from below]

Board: 2 copper layers, 99.8 x 80.0 mm, 30 parts (4 on the bottom side), 66 nets.
